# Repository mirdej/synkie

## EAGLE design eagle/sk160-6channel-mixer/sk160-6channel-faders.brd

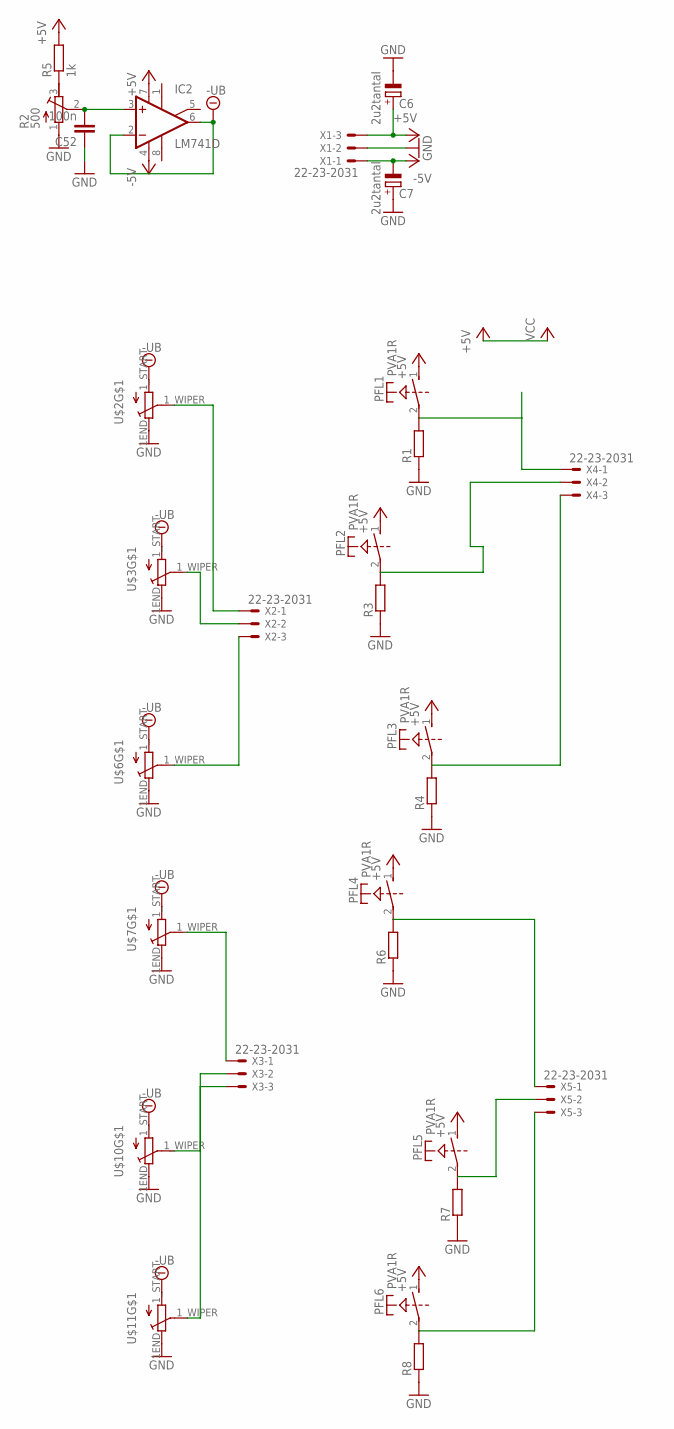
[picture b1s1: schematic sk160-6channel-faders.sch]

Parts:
C6, C7: 2u2tantal; CT3528
C52: 100n; C0805
IC2: LM741D; SO08
PFL1, PFL2, PFL3, PFL4, PFL5, PFL6: PVA1R
R1, R3, R4, R6, R7, R8: R-EU_R1206; R1206
R2: 500; RTRIM64Y
R5: 1k; R1206
U$2, U$3, U$6, U$7, U$10, U$11: ALPS_FADER_STEREO; ALPS_FADER_60MM
X1, X2, X3, X4, X5: 22-23-2031

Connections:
+5V: C6.+, IC2.7 (V+), PFL1.1 (S), PFL2.1 (S), PFL3.1 (S), PFL4.1 (S), PFL5.1 (S), PFL6.1 (S), R5.2, X1.3
-5V: C7.-, IC2.4 (V-), X1.1
-UB: IC2.2 (-IN), IC2.6 (OUT), U$2.1_START (S), U$3.1_START (S), U$6.1_START (S), U$7.1_START (S), U$10.1_START (S), U$11.1_START (S)
GND: C6.-, C7.+, C52.1, R1.1, R2.1 (E), R3.1, R4.1, R6.1, R7.1, R8.1, U$2.1END (E), U$3.1END (E), U$6.1END (E), U$7.1END (E), U$10.1END (E), U$11.1END (E), X1.2
unnamed: U$6.1_WIPER (W), X2.3
unnamed: PFL1.2, R1.2, X4.1
unnamed: PFL3.2, R4.2, X4.3
unnamed: PFL4.2, R6.2, X5.1
unnamed: PFL5.2, R7.2, X5.2
unnamed: PFL6.2, R8.2, X5.3
unnamed: U$2.1_WIPER (W), X2.1
unnamed: R2.3 (A), R5.1
unnamed: C52.2, IC2.3 (+IN), R2.2 (S)
unnamed: U$3.1_WIPER (W), X2.2
unnamed: U$7.1_WIPER (W), X3.1
unnamed: PFL2.2, R3.2, X4.2
unnamed: U$10.1_WIPER (W), X3.2
unnamed: U$11.1_WIPER (W), X3.3

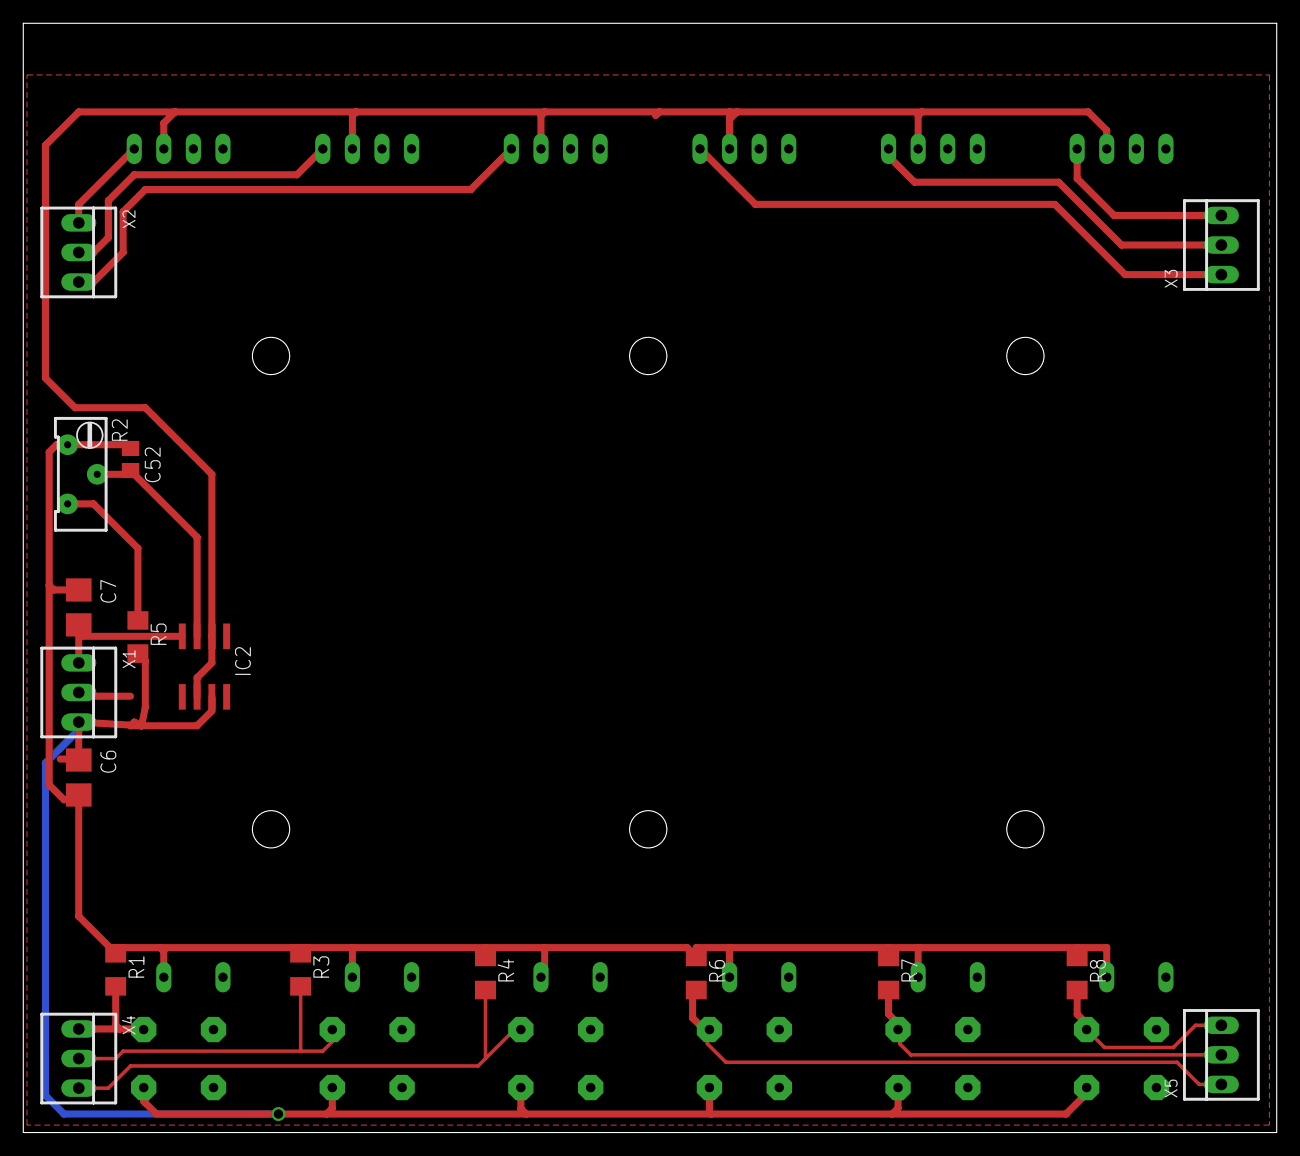
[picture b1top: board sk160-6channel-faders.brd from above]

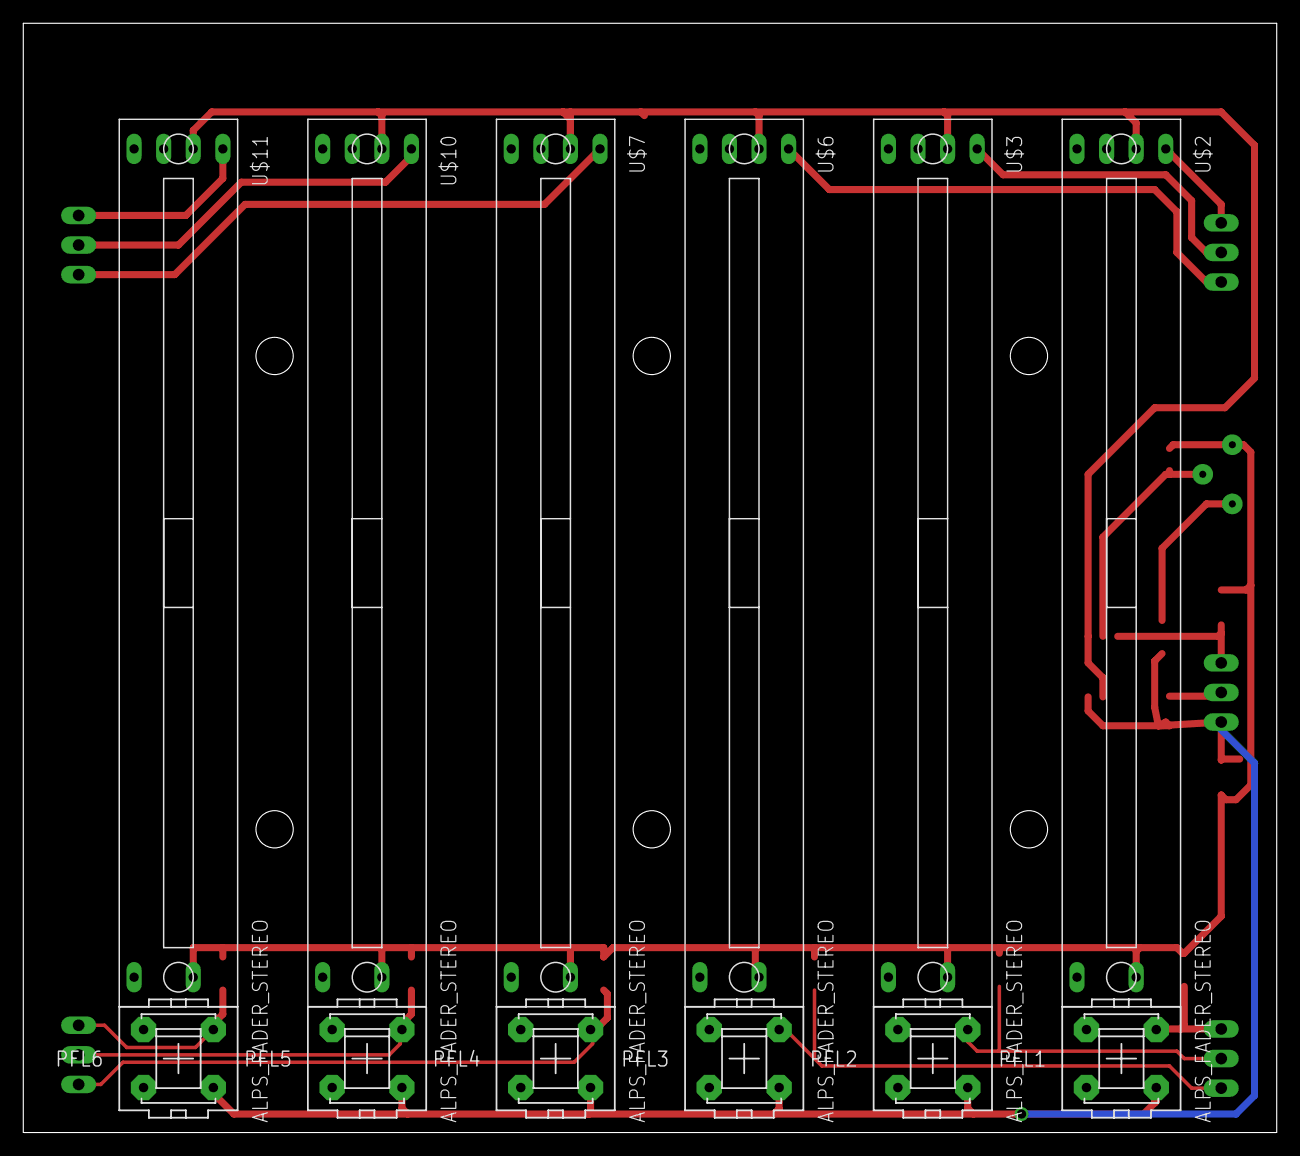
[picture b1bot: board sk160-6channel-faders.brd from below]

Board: 2 copper layers, 107.6 x 95.2 mm, 29 parts (12 on the bottom side), 18 nets.

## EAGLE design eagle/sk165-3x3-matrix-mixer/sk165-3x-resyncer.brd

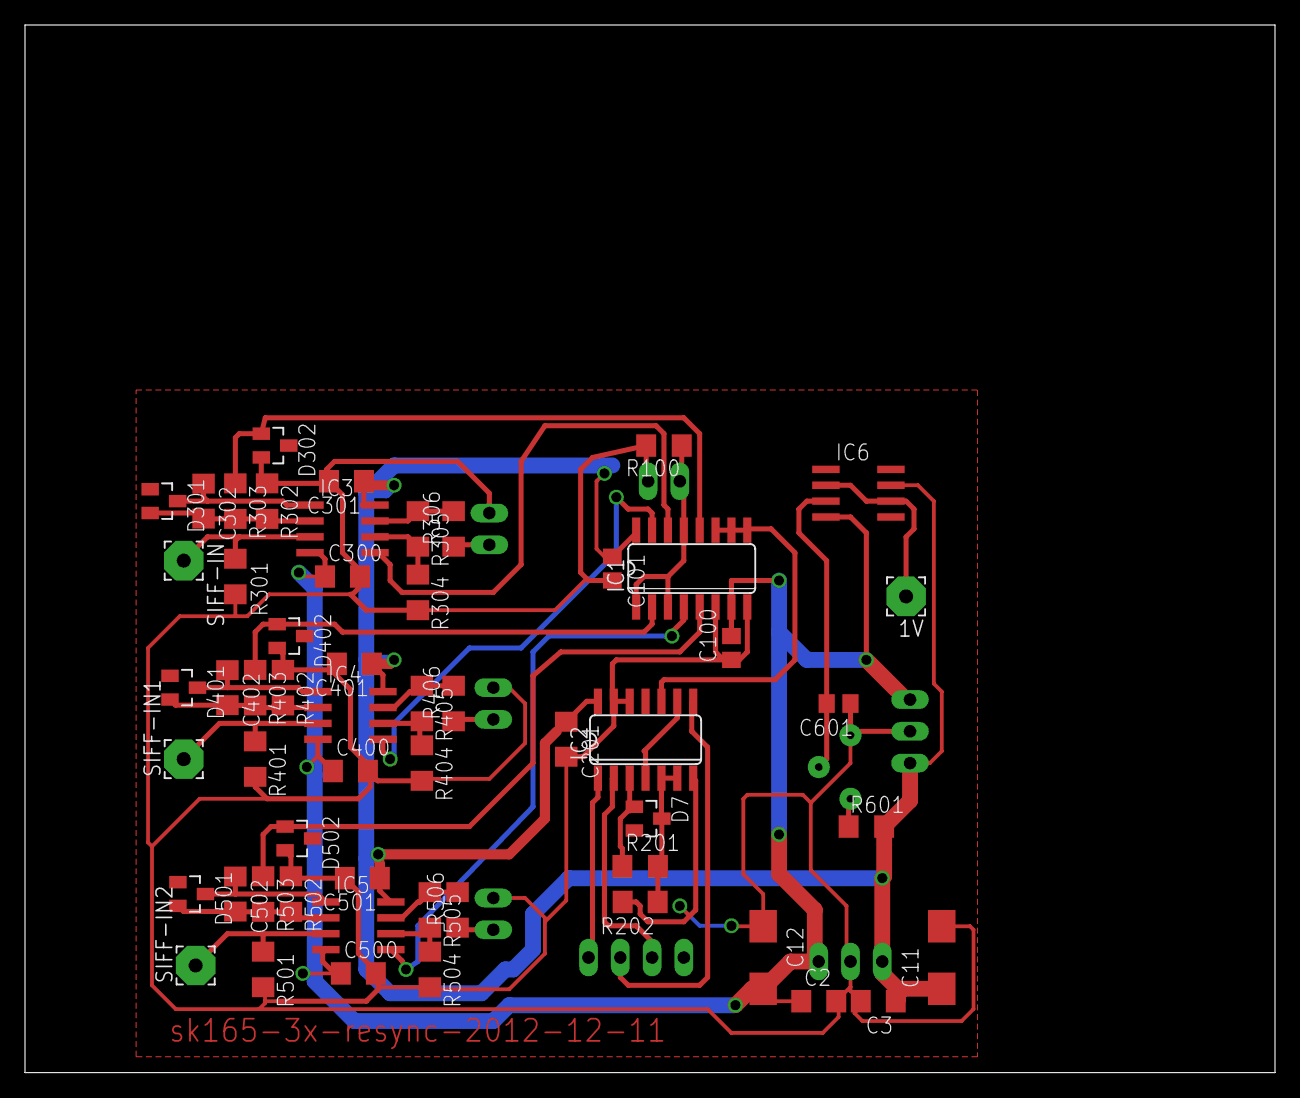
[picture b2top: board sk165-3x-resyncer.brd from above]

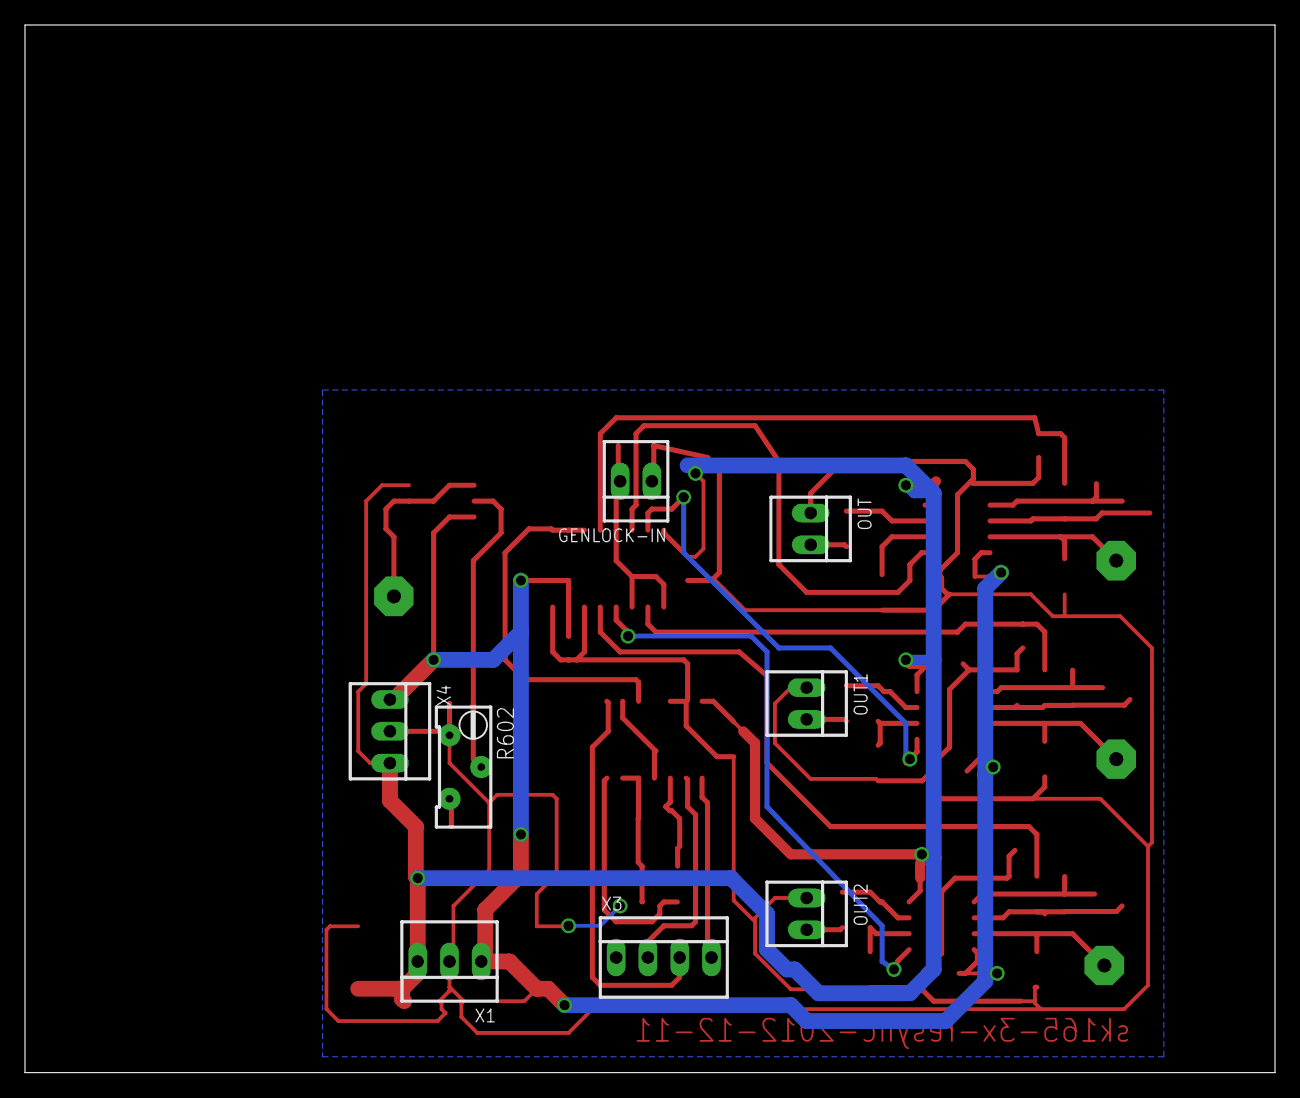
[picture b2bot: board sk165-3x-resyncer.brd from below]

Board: 2 copper layers, 100.0 x 83.8 mm, 64 parts (8 on the bottom side), 38 nets.

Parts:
1V: 3,17/1,1
C2, C3, C201, C300, C301, C400, C401, C500, C501: 100n; C1206
C11, C12: CT6032
C100, C101, C601: 100n; C0805
C302, C402, C502: 10p; C1206
D7: BAS70-04; SOT23
D301, D401, D501: BAT54S-L44; SOT23
D302, D402, D502: 1PS302; SOT23
GENLOCK-IN: 22-23-2021
IC1: 4053D; SO16
IC2: 4011D; SO14
IC3, IC4, IC5: LMH6643MA; SO08
IC6: LM741D; SO08
OUT, OUT1, OUT2: 22-23-2021
R100, R301, R401, R501: 47k; R1206
R201: 2k2; R1206
R202: 120p; C1206
R302, R303, R402, R403, R502, R503, R601: 1k; R1206
R304, R305, R404, R405, R504, R505: 200; R1206
R306, R406, R506: 75; R1206
R602: 500; RTRIM64Y
SIFF-IN, SIFF-IN1, SIFF-IN2: 3,17/1,1
X1, X4: 22-23-2031
X3: 22-23-2041

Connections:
+5V: C3.1, C11.+, C101.1, C201.1, C301.1, C401.1, C501.1, IC1.16, IC2.14, IC3.8, IC4.8, IC5.8, IC6.7, R601.2, X1.3, X4.3
-5V: C2.1, C12.-, C100.2, C300.1, C400.1, C500.1, IC1.7, IC3.4, IC4.4, IC5.4, IC6.4, X1.1, X4.1
-UB: 1V.1, IC6.2, IC6.6
AGND: C2.2, C3.2, C11.-, C12.+, C100.1, C101.2, C201.2, C300.2, C301.2, C400.2, C401.2, C500.2, C501.2, C601.1, D302.2, D402.2, D502.2, GENLOCK-IN.1, IC1.6, IC1.8, IC2.7, IC2.12, IC2.13, OUT.1, OUT1.1, OUT2.1, R100.2, R202.2, R301.2, R302.1, R304.2, R401.2, R402.1, R404.2, R501.2, R502.1, R504.2, R602.1, X1.2, X4.2
BACKPORCH: IC2.2, X3.2
D201: D7.3, IC2.5, IC2.6, R201.2, R202.1
H-SYNC: IC2.1, X3.4
unnamed: D402.1, IC1.2, R403.1
unnamed: IC4.3, R401.1, SIFF-IN1.1
unnamed: C402.1, D401.3, IC4.1
unnamed: GENLOCK-IN.2, IC1.1, IC1.3, IC1.13, R100.1
unnamed: C402.2, D401.2, IC4.2, R402.2, R403.2
unnamed: IC4.6, R404.1, R405.2
unnamed: IC4.7, R405.1, R406.2
unnamed: D302.1, IC1.12, R303.1
unnamed: IC2.4, IC2.9
unnamed: D7.1, IC2.3, R201.1
unnamed: D502.1, IC1.5, R503.1
unnamed: OUT1.2, R406.1
unnamed: IC1.9, IC1.10, IC1.11, IC2.10
unnamed: C302.1, D301.3, IC3.1
unnamed: IC3.3, R301.1, SIFF-IN.1
unnamed: IC1.15, IC4.5
unnamed: C302.2, D301.2, IC3.2, R302.2, R303.2
unnamed: IC5.3, R501.1, SIFF-IN2.1
unnamed: C502.1, D501.3, IC5.1
unnamed: C502.2, D501.2, IC5.2, R502.2, R503.2
unnamed: IC5.6, R504.1, R505.2
unnamed: IC3.6, R304.1, R305.2
unnamed: IC3.7, R305.1, R306.2
unnamed: IC1.14, IC3.5
unnamed: IC5.7, R505.1, R506.2
unnamed: IC1.4, IC5.5
unnamed: OUT2.2, R506.1
unnamed: OUT.2, R306.1
unnamed: R601.1, R602.3
unnamed: C601.2, IC6.3, R602.2
V-SYNC: IC2.8, X3.3

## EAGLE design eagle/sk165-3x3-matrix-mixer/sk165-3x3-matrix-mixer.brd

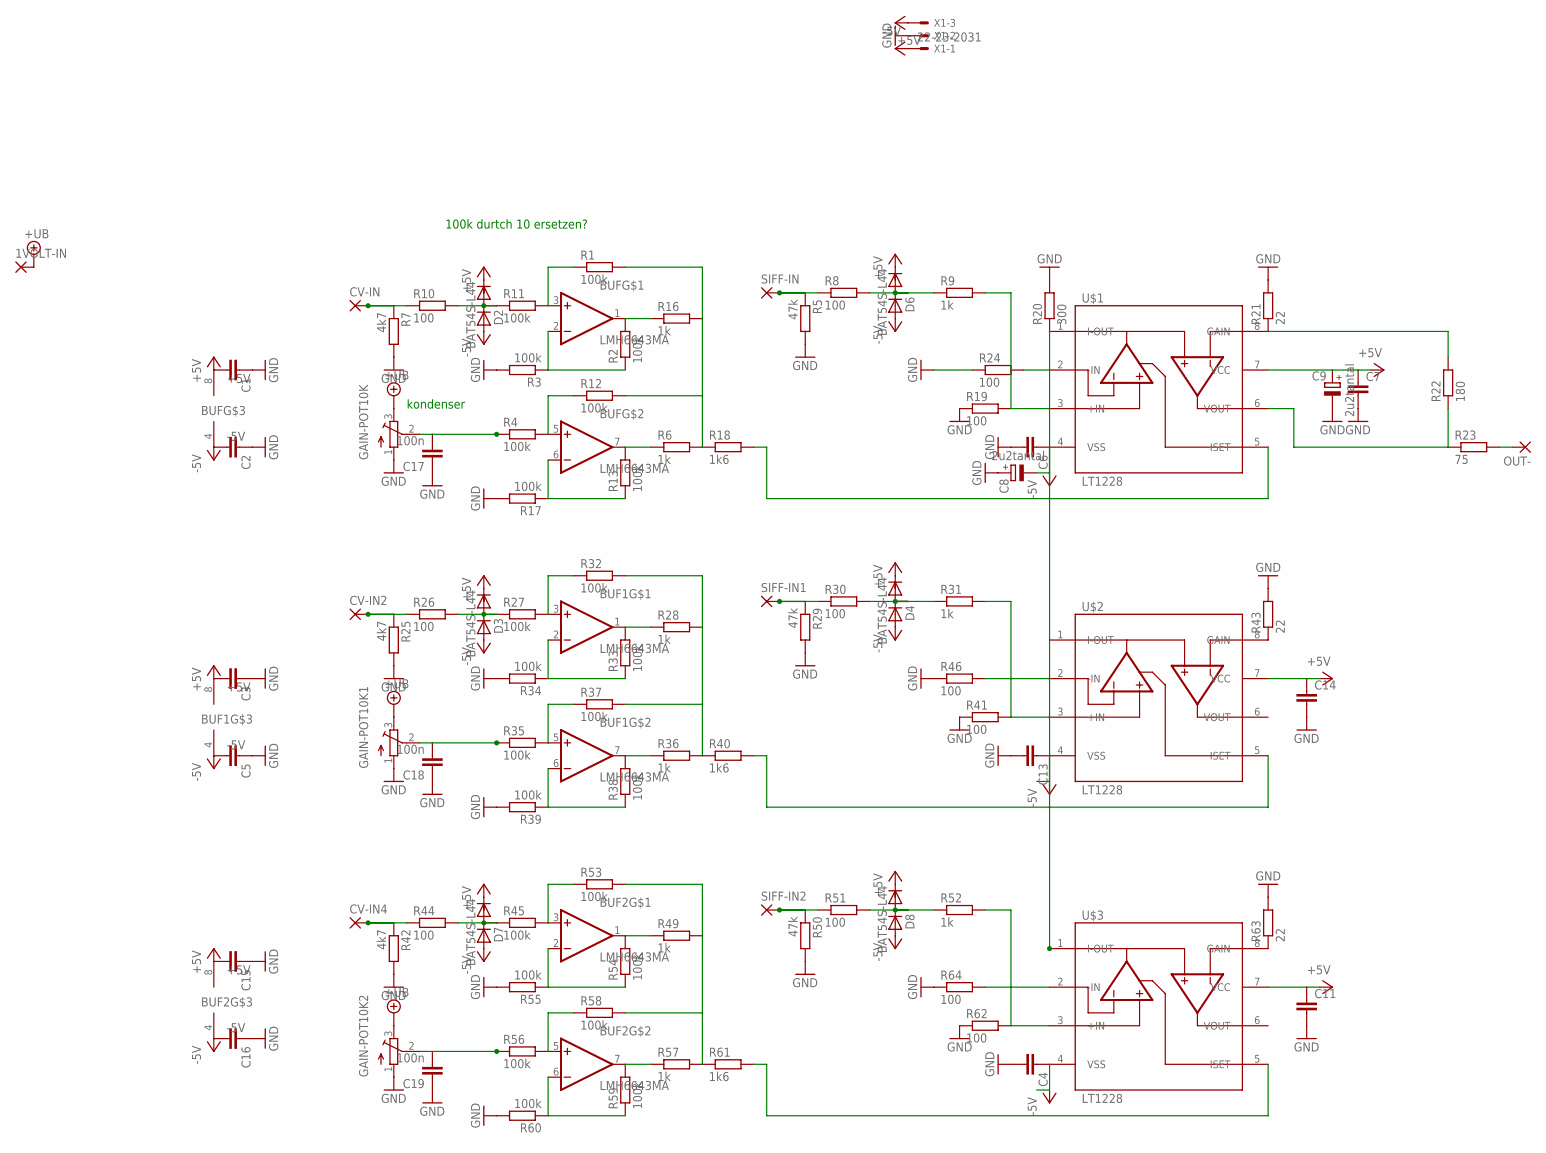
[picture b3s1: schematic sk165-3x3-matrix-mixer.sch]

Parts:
1VOLT-IN: 3,17/1,1
BUF, BUF1, BUF2: LMH6643MA; SO08
C1, C2, C3, C4, C5, C6, C7, C11, C13, C14, C15, C16: C-EUC1206; C1206
C8, C9: 2u2tantal; CT6032
C17, C18, C19: 100n; C1206
CV-IN, CV-IN2, CV-IN4: 3,17/1,1
D2, D3, D4, D6, D7, D8: BAT54S-L44; SOT23
GAIN-POT10K, GAIN-POT10K1, GAIN-POT10K2: 10k; ALPS_RK09K111
OUT-: 3,17/1,1
R1, R2, R3, R4, R11, R12, R13, R17, R27, R32, R33, R34, R35, R37, R38, R39, R45, R53, R54, R55, R56, R58, R59, R60: 100k; R1206
R5, R29, R50: 47k; R1206
R6, R9, R16, R28, R31, R36, R49, R52, R57: 1k; R1206
R7, R25, R42: 4k7; R1206
R8, R10, R19, R24, R26, R30, R41, R44, R46, R51, R62, R64: 100; R1206
R18, R40, R61: 1k6; R1206
R20: 300; R1206
R21, R43, R63: 22; R1206
R22: 180; R1206
R23: 75; R1206
SIFF-IN, SIFF-IN1, SIFF-IN2: 3,17/1,1
U$1, U$2, U$3: LT1228; SO08
X1: 22-23-2031

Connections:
+5V: BUF.8 (+5V), BUF1.8 (+5V), BUF2.8 (+5V), C1.2, C3.2, C7.1, C9.+, C11.1, C14.1, C15.2, D2.2 (C), D3.2 (C), D4.2 (C), D6.2 (C), D7.2 (C), D8.2 (C), U$1.7 (VCC), U$2.7 (VCC), U$3.7 (VCC), X1.3
+UB: 1VOLT-IN.1, GAIN-POT10K.3 (E), GAIN-POT10K1.3 (E), GAIN-POT10K2.3 (E)
-5V: BUF.4 (-5V), BUF1.4 (-5V), BUF2.4 (-5V), C2.2, C4.1, C5.2, C6.1, C8.-, C13.1, C16.2, D2.1 (A), D3.1 (A), D4.1 (A), D6.1 (A), D7.1 (A), D8.1 (A), U$1.4 (VSS), U$2.4 (VSS), U$3.4 (VSS), X1.1
GND: C1.1, C2.1, C3.1, C4.2, C5.1, C6.2, C7.2, C8.+, C9.-, C11.2, C13.2, C14.2, C15.1, C16.1, C17.1, C18.1, C19.1, GAIN-POT10K.1 (S), GAIN-POT10K1.1 (S), GAIN-POT10K2.1 (S), R3.2, R5.2, R7.2, R17.2, R19.1, R20.2, R21.2, R24.1, R25.2, R29.2, R34.2, R39.2, R41.1, R42.2, R43.2, R46.1, R50.2, R55.2, R60.2, R62.1, R63.2, R64.1, X1.2
unnamed: C17.2, GAIN-POT10K.2 (W), R4.1
unnamed: C18.2, GAIN-POT10K1.2 (W), R35.1
unnamed: CV-IN2.1, R25.1, R26.1
unnamed: BUF.2 (-IN), R2.1, R3.1
unnamed: R9.2, R19.2, U$1.3 (+IN)
unnamed: CV-IN4.1, R42.1, R44.1
unnamed: BUF.5 (+IN), R4.2, R12.1
unnamed: BUF.7 (OUT), R6.1, R13.2
unnamed: R21.1, R22.2, U$1.8 (GAIN)
unnamed: CV-IN.1, R7.1, R10.1
unnamed: D2.3 (AC), R10.2, R11.1
unnamed: BUF.6 (-IN), R13.1, R17.1
unnamed: D3.3 (AC), R26.2, R27.1
unnamed: BUF.3 (+IN), R1.1, R11.2
unnamed: R5.1, R8.1, SIFF-IN.1
unnamed: D6.3 (AC), R8.2, R9.1
unnamed: BUF.1 (OUT), R2.2, R16.1
unnamed: R18.2, U$1.5 (ISET)
unnamed: R1.2, R6.2, R12.2, R16.2, R18.1
unnamed: R22.1, R23.1, U$1.6 (VOUT)
unnamed: OUT-.1, R23.2
unnamed: R24.2, U$1.2 (-IN)
unnamed: BUF1.3 (+IN), R27.2, R32.1
unnamed: BUF1.1 (OUT), R28.1, R33.2
unnamed: R28.2, R32.2, R36.2, R37.2, R40.1
unnamed: R29.1, R30.1, SIFF-IN1.1
unnamed: D4.3 (AC), R30.2, R31.1
unnamed: R31.2, R41.2, U$2.3 (+IN)
unnamed: BUF1.2 (-IN), R33.1, R34.1
unnamed: BUF1.5 (+IN), R35.2, R37.1
unnamed: BUF1.7 (OUT), R36.1, R38.2
unnamed: BUF1.6 (-IN), R38.1, R39.1
unnamed: R40.2, U$2.5 (ISET)
unnamed: R20.1, U$1.1 (I-OUT), U$2.1 (I-OUT), U$3.1 (I-OUT)
unnamed: D7.3 (AC), R44.2, R45.1
unnamed: BUF2.3 (+IN), R45.2, R53.1
unnamed: BUF2.1 (OUT), R49.1, R54.2
unnamed: R46.2, U$2.2 (-IN)
unnamed: C19.2, GAIN-POT10K2.2 (W), R56.1
unnamed: R49.2, R53.2, R57.2, R58.2, R61.1
unnamed: R43.1, U$2.8 (GAIN)
unnamed: R50.1, R51.1, SIFF-IN2.1
unnamed: D8.3 (AC), R51.2, R52.1
unnamed: R52.2, R62.2, U$3.3 (+IN)
unnamed: BUF2.2 (-IN), R54.1, R55.1
unnamed: BUF2.5 (+IN), R56.2, R58.1
unnamed: BUF2.7 (OUT), R57.1, R59.2
unnamed: BUF2.6 (-IN), R59.1, R60.1
unnamed: R61.2, U$3.5 (ISET)
unnamed: R64.2, U$3.2 (-IN)
unnamed: R63.1, U$3.8 (GAIN)

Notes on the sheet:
100k durtch 10 ersetzen?
kondenser

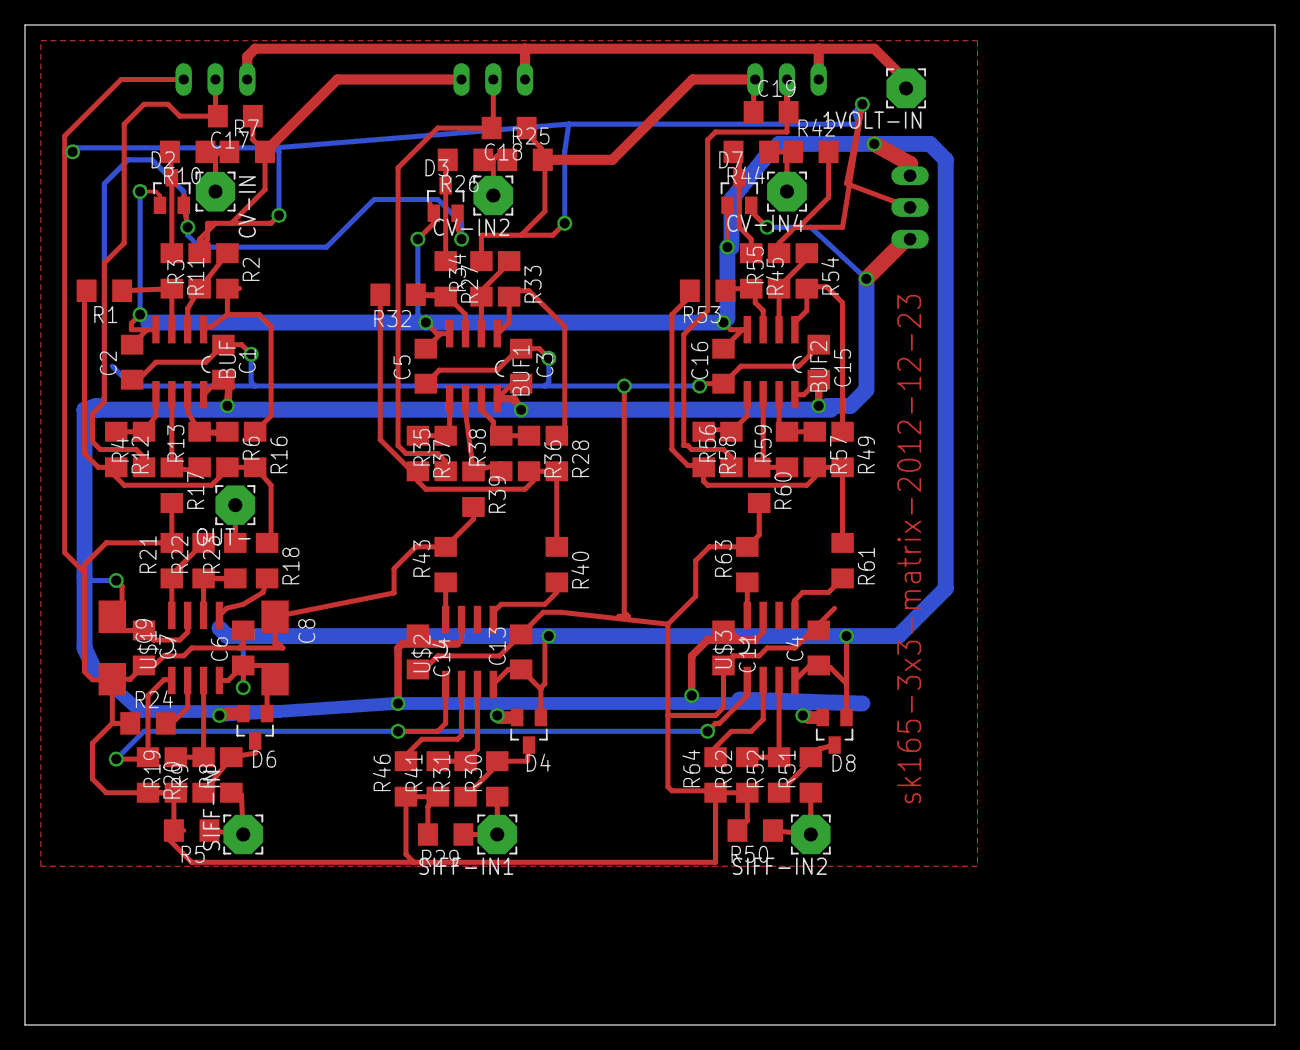
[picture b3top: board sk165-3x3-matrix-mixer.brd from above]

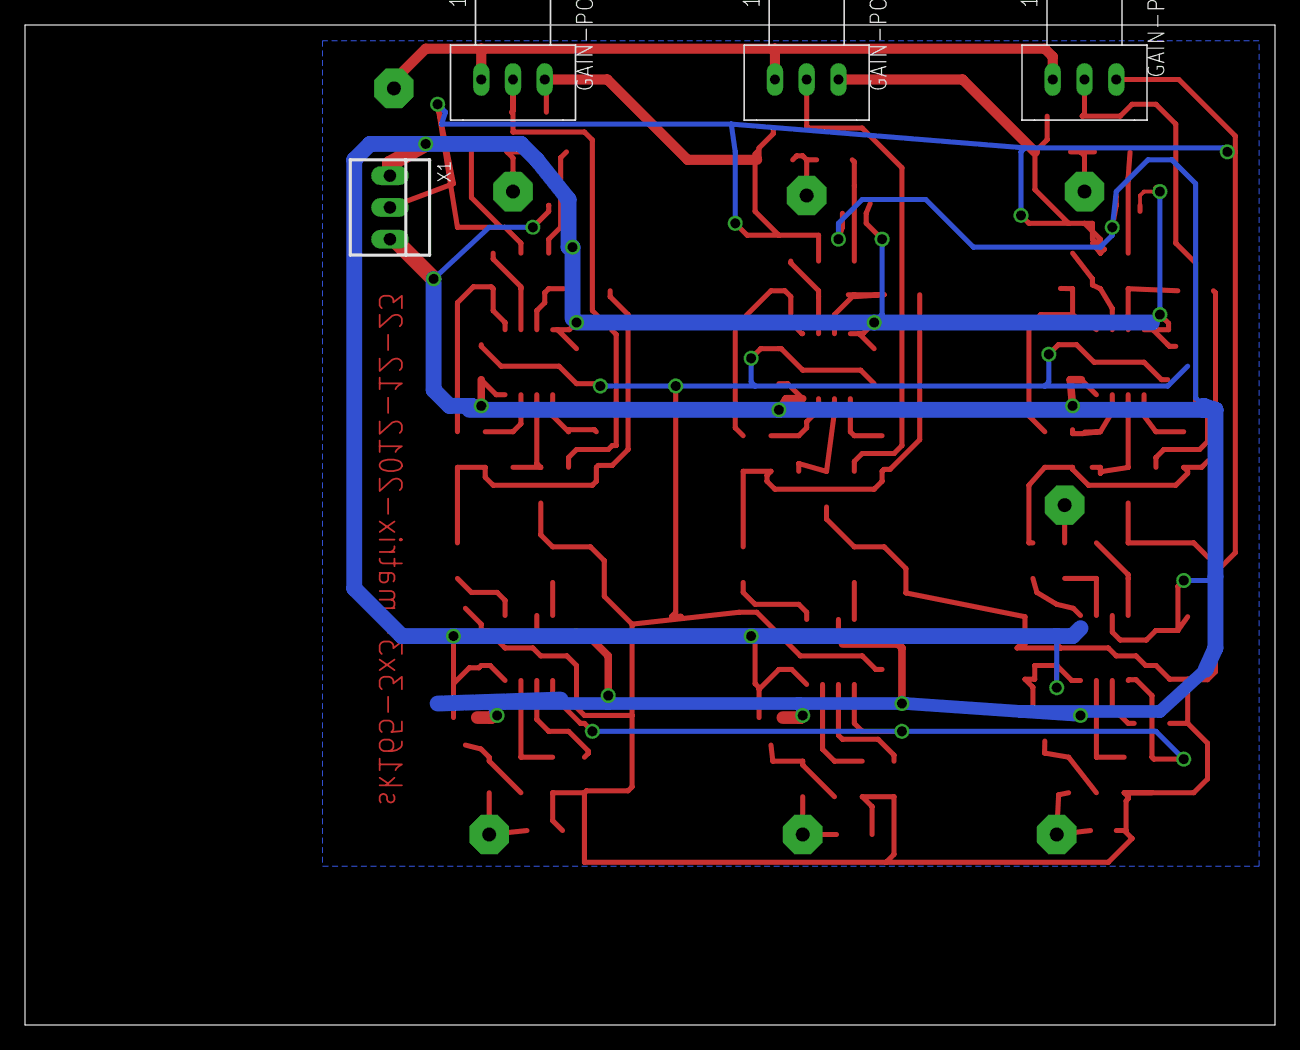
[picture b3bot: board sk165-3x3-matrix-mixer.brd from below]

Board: 2 copper layers, 100.0 x 80.0 mm, 101 parts (4 on the bottom side), 55 nets.

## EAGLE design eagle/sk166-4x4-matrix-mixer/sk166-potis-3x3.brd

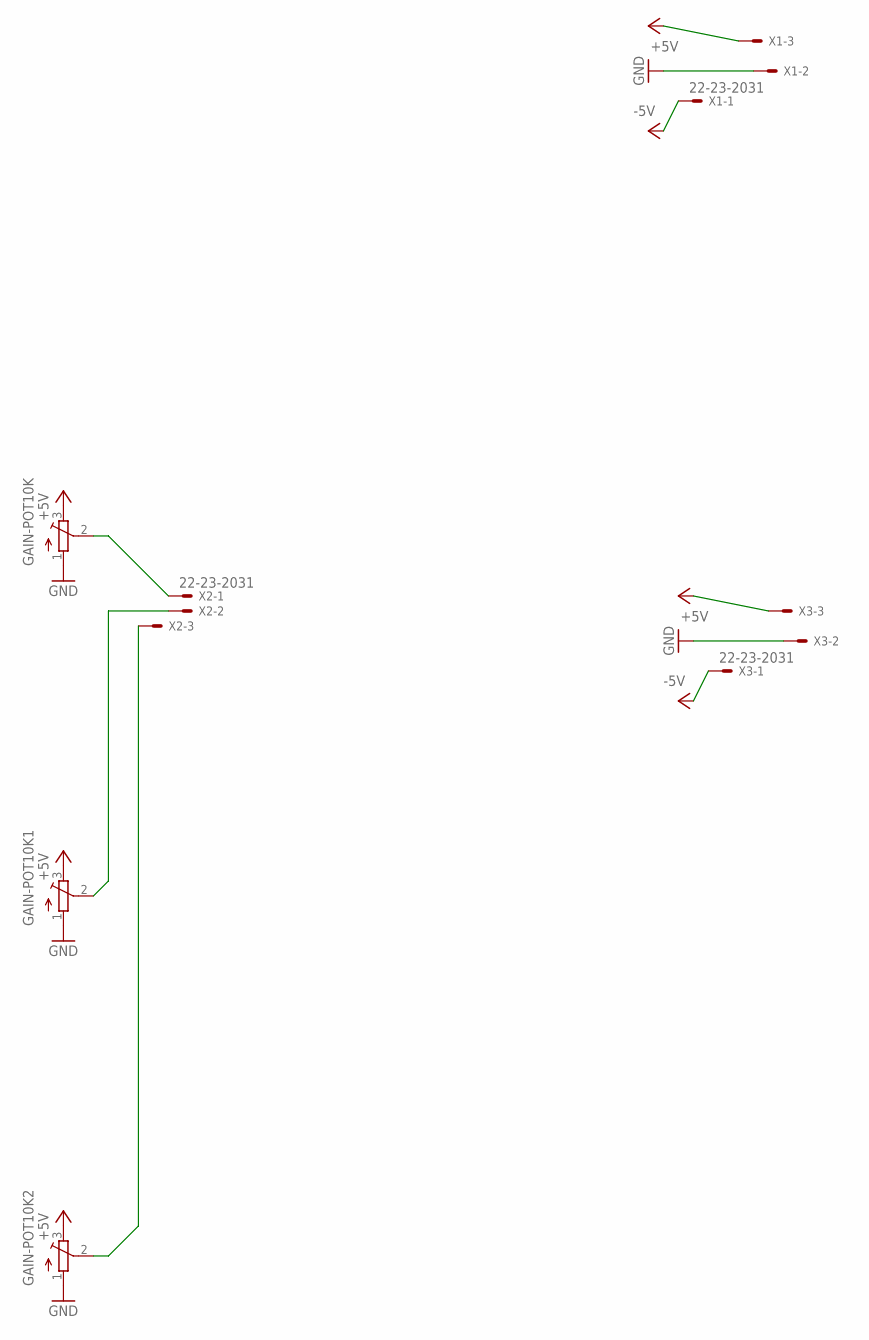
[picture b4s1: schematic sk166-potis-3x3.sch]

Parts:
GAIN-POT10K, GAIN-POT10K1, GAIN-POT10K2: 10k; ALPS_RK09K111
X1, X2, X3: 22-23-2031

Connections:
+5V: GAIN-POT10K.3 (E), GAIN-POT10K1.3 (E), GAIN-POT10K2.3 (E), X1.3, X3.3
-5V: X1.1, X3.1
GND: GAIN-POT10K.1 (S), GAIN-POT10K1.1 (S), GAIN-POT10K2.1 (S), X1.2, X3.2
unnamed: GAIN-POT10K.2 (W), X2.1
unnamed: GAIN-POT10K1.2 (W), X2.2
unnamed: GAIN-POT10K2.2 (W), X2.3

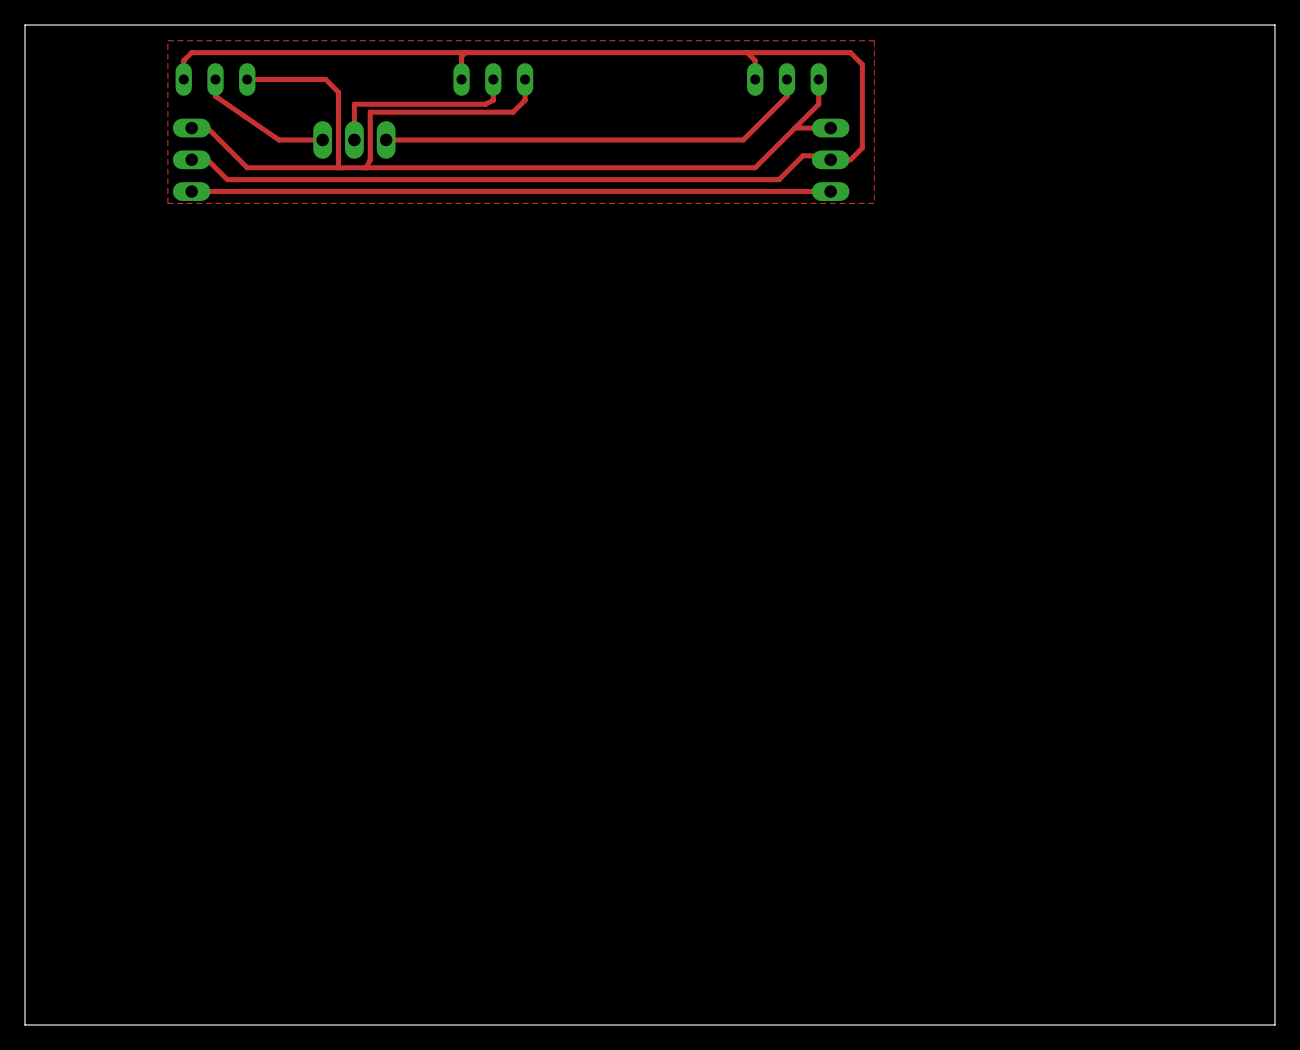
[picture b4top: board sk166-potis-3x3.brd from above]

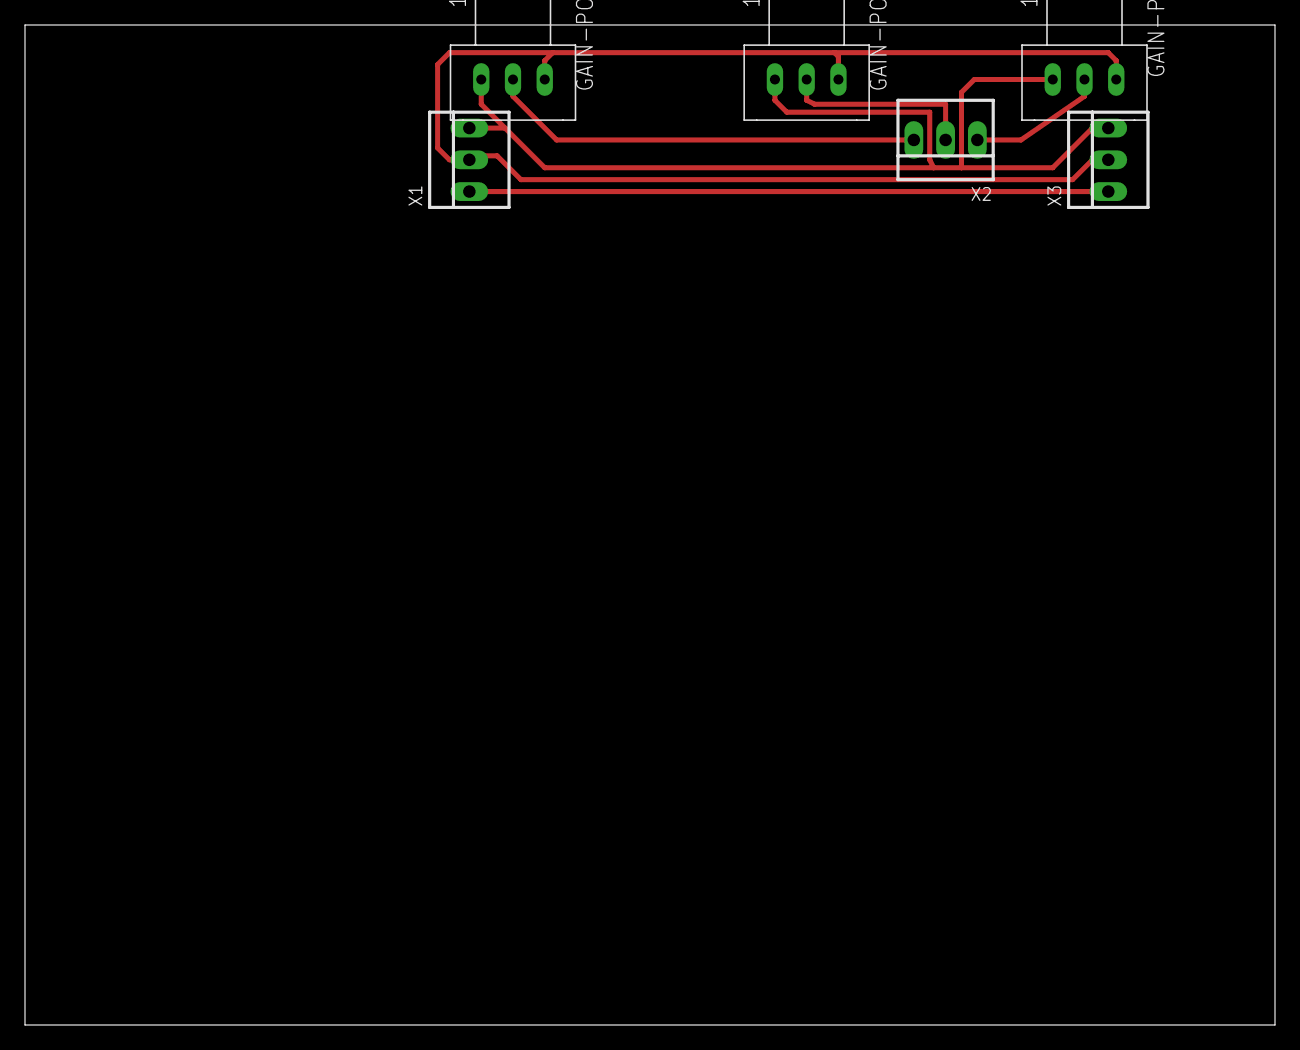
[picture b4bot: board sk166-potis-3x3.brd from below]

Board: 2 copper layers, 100.0 x 80.0 mm, 6 parts (6 on the bottom side), 6 nets.

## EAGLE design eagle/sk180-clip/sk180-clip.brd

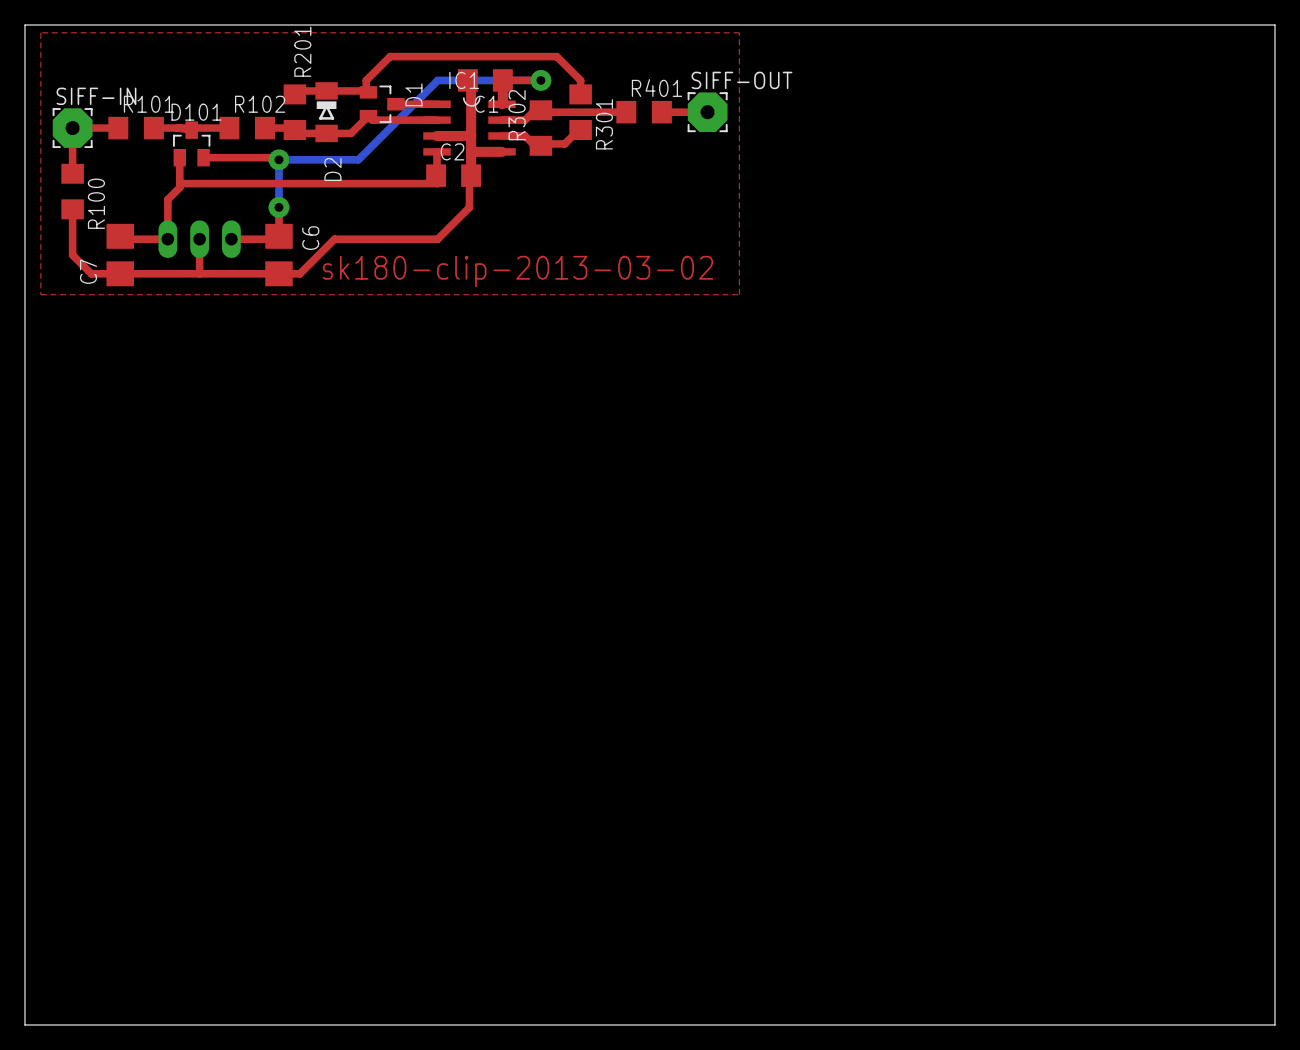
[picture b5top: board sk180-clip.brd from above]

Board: 2 copper layers, 100.0 x 80.0 mm, 18 parts (1 on the bottom side), 11 nets.

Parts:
C1, C2: C1206
C6, C7: 2u2tantal; CT3528
D1, D101: BAT54S-L44; SOT23
D2: MINIMELF
IC1: MAX4392ESA; SO08
R100: 47k; R1206
R101: 100; R1206
R102, R201, R301, R302: 6k8; R1206
R401: 75; R1206
SIFF-IN: 3,17/1,1
SIFF-OUT: 3,17/1,1
X1: 22-23-2031

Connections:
+5V: C1.1, C6.+, D101.2, IC1.8, X1.3
-5V: C2.1, C7.-, D101.1, IC1.4, X1.1
GND: C1.2, C2.2, C6.-, C7.+, IC1.3, IC1.5, R100.2, X1.2
unnamed: D1.2, D2.A, IC1.2, R102.2, R201.1
unnamed: D1.3, IC1.1
unnamed: D1.1, D2.C, R201.2, R301.1
unnamed: IC1.6, R301.2, R302.1
unnamed: IC1.7, R302.2, R401.1
unnamed: R401.2, SIFF-OUT.1
unnamed: R100.1, R101.1, SIFF-IN.1
unnamed: D101.3, R101.2, R102.1
